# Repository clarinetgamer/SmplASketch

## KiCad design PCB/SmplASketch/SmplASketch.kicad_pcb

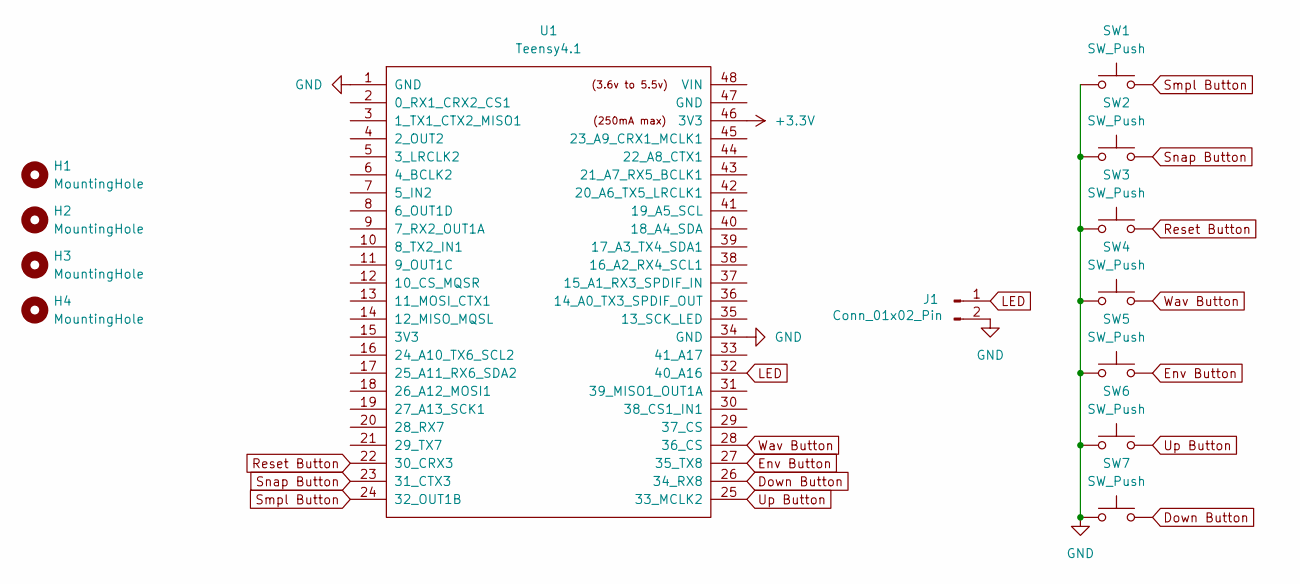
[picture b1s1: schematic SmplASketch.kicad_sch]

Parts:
H1, H2, H3, H4: MountingHole; MountingHole_2.7mm
J1: Conn_01x02_Pin; PinSocket_1x02_P2.54mm_Vertical
SW1, SW2, SW3, SW4, SW5, SW6, SW7: SW_Push; SW_Cherry_MX_1.00u_PCB
U1: Teensy4.1; Teensy41

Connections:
+3.3V: U1.46 (3V3)
Down Button: SW7.2, U1.26 (34_RX8)
Env Button: SW5.2, U1.27 (35_TX8)
GND: J1.2, SW1.1, SW2.1, SW3.1, SW4.1, SW5.1, SW6.1, SW7.1, U1.1 (GND), U1.34 (GND)
LED: J1.1, U1.32 (40_A16)
Reset Button: SW3.2, U1.22 (30_CRX3)
Smpl Button: SW1.2, U1.24 (32_OUT1B)
Snap Button: SW2.2, U1.23 (31_CTX3)
Up Button: SW6.2, U1.25 (33_MCLK2)
Wav Button: SW4.2, U1.28 (36_CS)

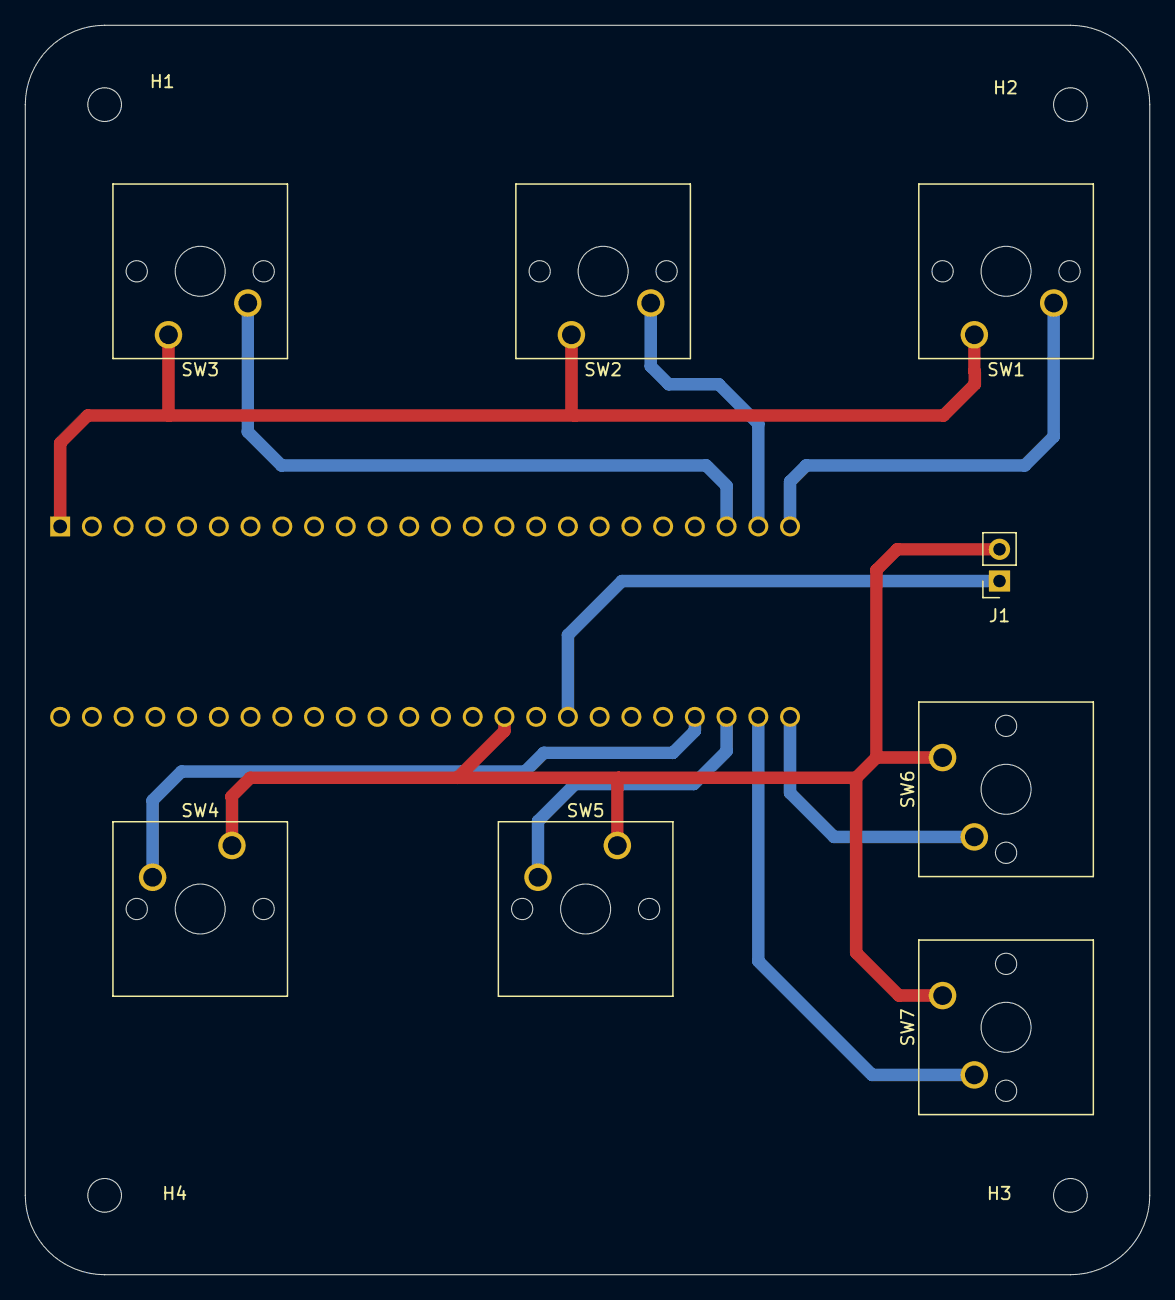
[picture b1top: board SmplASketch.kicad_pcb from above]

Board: 2 copper layers, 90.0 x 100.0 mm, 13 parts (1 on the bottom side), 9 nets.

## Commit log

2025-09-20 C++ Keyboard Control Code
2025-09-20 Added Microcontroller Breadboard Picture
2025-09-22 UI Goodies
    -Knob Control
    -Wav/env displays
2025-09-22 More UI!
    Kinda looks like a thing now
    Also added mode swapping
2025-09-22 Made knobs more user friendly
    also added comments to UI code
2025-09-23 icon update
2025-09-23 Cookin
    -Fixed bugs from combining UI with internal code
    -Fixed reset feature
    -Fixed size of cam constraint vs size of ui bug
    -LOOKS COOL!
2025-09-23 Ascii comunication
2025-09-23 Cache Handling
    -And exit with escape
2025-09-23 Bug Fixes
    There is a random bug that I cannot for the life of me solve that I think is actually a processing bug in which .amp() does not actually change the amplitude of an audio sample device
2025-09-23 WE DID IT
    fixed the volume bug
2025-09-23 Added MacOS Download 4 Progress Check
    Reorganized GitHub As Well
2025-09-23 Fixed Old Documentation
2025-09-23 Removed Download Option
    need to figure out how to sign applications for download
2025-09-23 Create YoutubeLink
2025-09-23 Documentation Upload/End of Week 3 Work
2025-09-24 Buttons/NewMenus
    Wrote code without GUI Builder to open help menu. Changed some graphics. Added help menu. Added framework for connection display.
2025-09-24 Condensed Tabs
2025-09-25 Tinkering
2025-09-25 PhotoWaveformWork
2025-09-26 Flash/PCB/Imgcode
2025-09-26 CAD Galore/Documentation
2025-09-26 Ordered PCB
2025-09-26 PCB Order
2025-09-29 Added UI for envelope editor
2025-09-29 User Input Class
2025-09-30 Envelope Menu Capability
2025-09-30 Missing file from last commit
2025-09-30 Fixed multiple windows bug
2025-10-01 Create Youtube
2025-10-01 Documentation
2025-10-02 Began fixing ascii communication need to finish
2025-10-03 Repaired ASCII communication with device
2025-10-03 Wav Menu design
2025-10-03 added basic wav editor ui
2025-10-04 ascii stuff other tests other fixes
2025-10-06 Modified to work with camera/new 3d prints
2025-10-07 Graphic Save
2025-10-07 Wav Menu Stuff
2025-10-08 WavMenuStuff
2025-10-08 Organization
2025-10-09 3dPrintFileUpdate
2025-10-09 In class work
2025-10-10 Finished WavMenu/Added Connection
2025-10-10 V1 of app is done and exported
    both test and device mode exports exist but are unsigned so most likely not downloadable from github
2025-10-10 exportsmodded
2025-10-10 Documentation Images
2025-10-10 comments
2025-10-14 Demo Video Mod Stuff
2025-10-14 Midterm Paper
2025-10-24 NewUI Basics
2025-10-25 Laser Cut
2025-10-25 laser cut update
2025-10-25 update pt 2
2025-10-25 update pt 3
2025-10-31 3D Printing and UI
2025-10-31 Remove exports folder
2025-10-31 stuff
2025-11-03 Opened pcb for ref
2025-11-03 porting functionality to new ui
    mode and vol knobs and general device functions work
    need to fix the other menus and add new stuff
2025-11-04 Envelope Menu/Beginnings of Calib Mode
2025-11-05 Calibration Stuff
2025-11-06 PhotoSynthesis+CalibMode
2025-11-06 Calib Image Reset Fixed
2025-11-06 Added Color Mode-Ish/Buttons
2025-11-07 Color Mode Finished
2025-11-07 Color Bug
    need to add cache clear fix
2025-11-09 Lots Of Stuff
    -Implemented Revised Pitch Control
    -Added More UI
    -Rewrote photosynthesis mode entirely
2025-11-09 Finished Photsynthesis Mode
2025-11-09 bugtweaks
2025-11-09 add line animation function
2025-11-10 Finish UI Start Hooking Up Remaining Buttons
2025-11-15 Calm before the rewrite....
2025-11-15 Lots and lots of stuff
    Completely gutted backend. Rewrote sampling code from scratch in minim. Rewrode envelope code to work with ADSR and in minim. Rewrote envelope display code. Added in playback head for envelope. And m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
2025-11-15 Reorganized code base fixed other various things
2025-11-15 Split GUI into 2 classes GUI and user input
2025-11-15 fixed errors in last commit
2025-11-16 Photosynthesis works with minim now
2025-11-16 LFO Mode DONE
2025-11-16 MP3 Export Fucntionality
2025-11-16 Fixed Save Error from last commit
2025-11-19 Lots of changes the past few days.
    -Did demos
    -text spacing
    -modified mp3 export
    -added UI intro to draw mode
    -other stuff I forgot about doing at this point
2025-11-21 Mini Draw Graphic
2025-12-04 Early Save Mode Implementation
2025-12-04 more save stuff
    need to fix vol/drawKnob
2025-12-04 more preset compatability
    need to add visual components for Wav/LFO Preset
2025-12-10 Recorded Tutorials/Uploaded Images
2025-12-10 Last Commit Of V2
